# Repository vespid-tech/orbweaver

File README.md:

# orbweaver

Orbweaver is a Sub-GHz HAT+ designed for the Raspberry Pi 5. When loaded with the Orbweaver firmware, it allows users to set-up peer-to-peer mesh networks between Raspberry Pi's, Desktop/Laptops, and Android mobile devices.

# Licensing & Trademarks

### Open Source Components
* **Hardware (`/hardware`)**: All hardware licensed under **CERN Open Hardware Licence Version 2 – Strongly Reciprocal** (`CERN-OHL-S-2.0`).
* **Firmware (`/firmware`)**: All firmware Licensed under the **GNU General Public License v3.0** (`GPL-3.0-only`).
* **Software (`/software`)**: All software Licensed under the **GNU General Public License v3.0** (`GPL-3.0-only`).
* **Documentation (`/documents`)**: All documentation (except the trademarks mentioned below) Licensed under the **Creative Commons Attribution-ShareAlike 4.0 International** (`CC BY-SA 4.0`).
* The full text of these licenses can be found in this repository in the hardware, software, and firmware folders they apply to.

### Non-open Source Components
* **Trademarks:** "Vespid," "Orbweaver," and associated logos are trademarks of Vespid.

# Questions, Info, Help

You can find out more about Vespid online at **[www.vespidtech.com](https://www.vespidtech.com)**.

# Disclaimer

Orbweaver is provided “as is,” without warranty of any kind express or implied. In no event shall Vespid or any Orbweaver developers or contributors be liable for any claim, damages, or other liability arising from its use. Orbweaver is intended for evaluation and development use only. It is not supplied as a finished product and is not certified for use in any product made for sale to the general public. The purchaser is responsible for ensuring that the final configuration (including but not limited to firmware configuration, transmission power, antenna selection, transmission frequency, etc.), complies with applicable regulatory requirements.

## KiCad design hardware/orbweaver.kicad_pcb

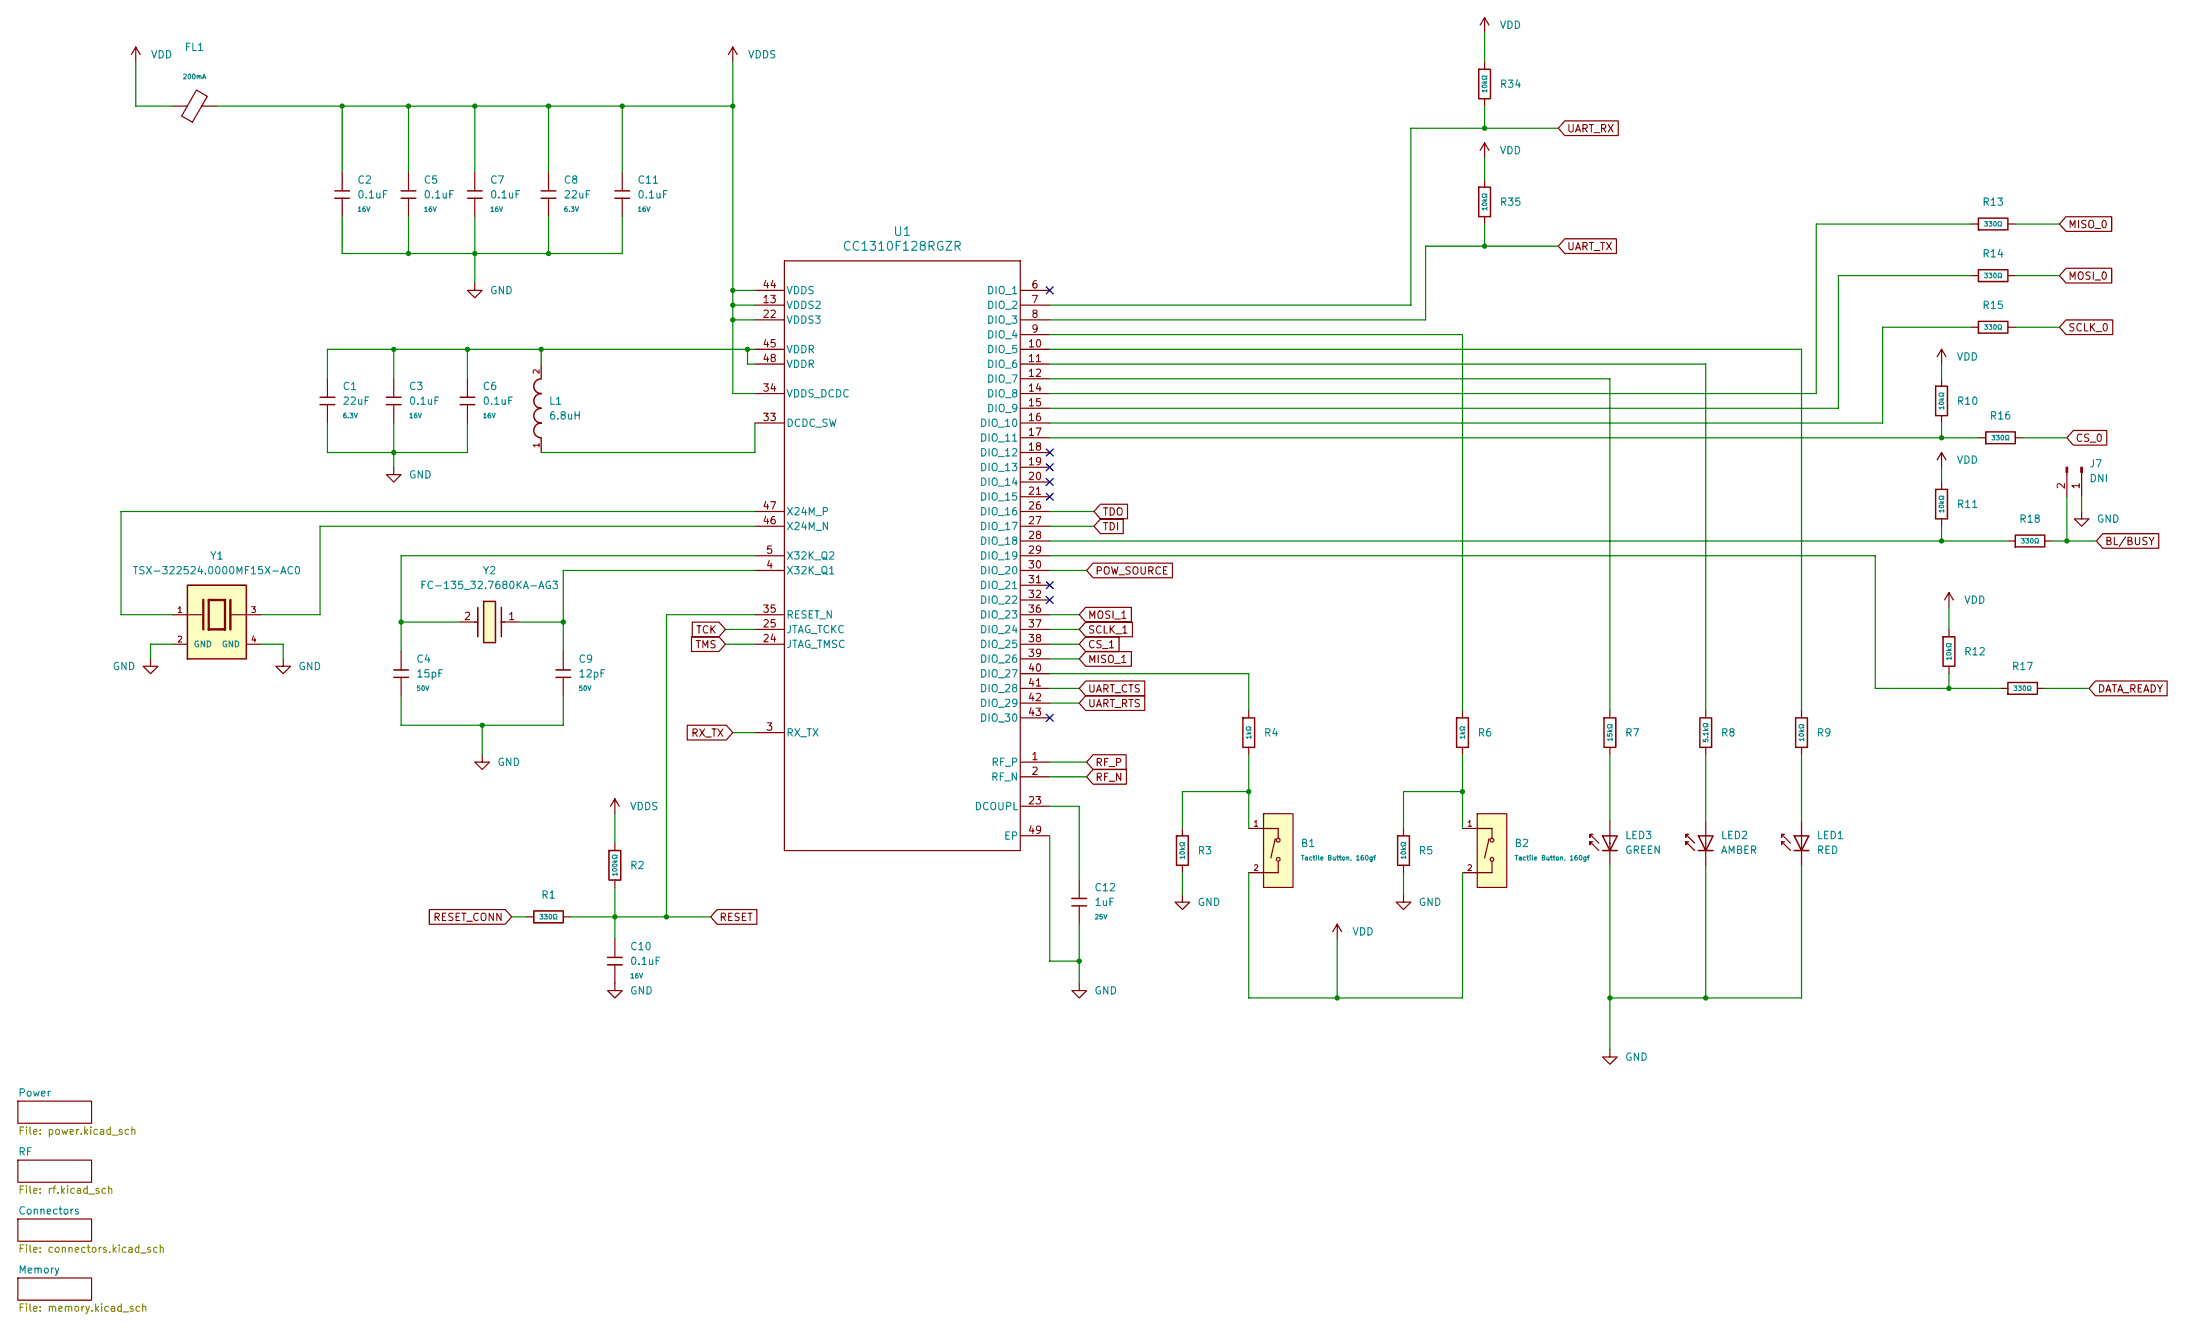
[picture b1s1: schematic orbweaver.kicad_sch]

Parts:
B1, B2: Tactile Button, 160gf; SW_TS-1088-AR02016; Voltage Rating (Dc) 12V; Part TS-1088-AR02016; LCSC C720477
C1, C8: 22uF; C_0603; Voltage Rated 6.3V; Tolerance ±20%; Part CL10A226MQ8NRNC; LCSC C59461
C2, C3, C5, C6, C7, C10, C11: 0.1uF; C_0402; Voltage Rated 16V; Tolerance ±10%; Part CL05B104KO5NNNC; LCSC C1525
C4: 15pF; C_0402; Voltage Rated 50V; Tolerance ±5%; Part 0402CG150J500NT; LCSC C1548
C9: 12pF; C_0402; Voltage Rated 50V; Tolerance ±5%; Part 0402CG120J500NT; LCSC C1547
C12: 1uF; C_0402; Voltage Rated 25V; Tolerance ±10%; Part CL05A105KA5NQNC; LCSC C52923
FL1: FB_0603; Current Rating 200mA; Tolerance ±25%; Part GZ1608D601TF; LCSC C1002
J7: DNI; PinHeader_1x02_P2.54mm_Vertical
L1: 6.8uH; INDC2012X105N; Mouser Part Number 810-MLZ2012N6R8LT000
LED1: RED; D_0805; Forward Voltage (VF) 1.6V~2.6V; Mouser Part Number 941-JE2835ARDN01AN
LED2: AMBER; D_0805; Mouser Part Number 941-JE2835ARDN01AN
LED3: GREEN; D_0805; Mouser Part Number 941-JE2835AGRN02AN
R1, R13, R14, R15, R16: 330Ω; R_0805; Overload Voltage (Max) 150V; Tolerance ±1%; Part 0805W8F1000T5E; LCSC C17408
R2: 100kΩ; R_0402; Overload Voltage (Max) 50V; Tolerance ±1%; Part 0402WGF1003TCE; DigiKey_Part_Number 541-CRCW0402100KFHEDPCT-ND
R3, R5, R9, R10, R11, R12, R34, R35: 10kΩ; R_0805; Overload Voltage (Max) 150V; Tolerance ±1%; Part 0805W8F1002T5E; LCSC C17414
R4, R6: 1kΩ; R_0805; Overload Voltage (Max) 150V; Tolerance ±1%; Part 0805W8F1001T5E; LCSC C17513
R7: 15kΩ; R_0805; Overload Voltage (Max) 150V; Tolerance ±1%; Part 0805W8F1502T5E; LCSC C17475
R8: 5.1kΩ; R_0805; Overload Voltage (Max) 150V; Tolerance ±1%; Part 0805W8F5101T5E; LCSC C27834
R17, R18: 330Ω; R_0805; Overload Voltage (Max) 150V; Tolerance ±1%; Part 0805W8F3300T5E; LCSC C17630
U1: CC1310F128RGZR; Texas_RGZ0048A_VQFN-48-1EP_7x7mm_P0.5mm_EP5.15x5.15mm
Y1: TSX-322524.0000MF15X-AC0; XTAL_TSX-3225_24.0000MF15X-AC0; PARTREV N/A
Y2: FC-135_32.7680KA-AG3; FC135327680KAAG3; Mouser Part Number 732-FC135-32.76KAAG3

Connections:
BL/BUSY: J7.2, R18.2; also elsewhere on the board
CS_0: R16.2; also elsewhere on the board
CS_1: U1.38 (DIO_25); also elsewhere on the board
DATA_READY: R17.2; also elsewhere on the board
GND: C1.1, C2.1, C3.1, C4.1, C5.1, C6.1, C7.1, C8.1, C9.1, C10.1, C11.1, C12.1, J7.1, LED1.1, LED2.1, LED3.1, R3.2, R5.2, U1.49 (EP), Y1.2 (GND), Y1.4 (GND); also elsewhere on the board
MISO_0: R13.2; also elsewhere on the board
MISO_1: U1.39 (DIO_26); also elsewhere on the board
MOSI_0: R14.2; also elsewhere on the board
MOSI_1: U1.36 (DIO_23); also elsewhere on the board
unnamed: B1.1 (A), R3.1, R4.2
unnamed: B2.1 (A), R5.1, R6.2
unnamed: C1.2, C3.2, C6.2, L1.2, U1.45 (VDDR), U1.48 (VDDR)
unnamed: LED1.2, R9.1
unnamed: LED2.2, R8.1
unnamed: LED3.2, R7.2
unnamed: L1.1, U1.33 (DCDC_SW)
unnamed: C12.2, U1.23 (DCOUPL)
unnamed: R6.1, U1.9 (DIO_4)
unnamed: R9.2, U1.10 (DIO_5)
unnamed: R8.2, U1.11 (DIO_6)
unnamed: R7.1, U1.12 (DIO_7)
unnamed: R13.1, U1.14 (DIO_8)
unnamed: R14.1, U1.15 (DIO_9)
unnamed: R15.1, U1.16 (DIO_10)
unnamed: R10.2, R16.1, U1.17 (DIO_11)
unnamed: R11.2, R18.1, U1.28 (DIO_18)
unnamed: R12.2, R17.1, U1.29 (DIO_19)
unnamed: R4.1, U1.40 (DIO_27)
unnamed: U1.46 (X24M_N), Y1.3
unnamed: U1.47 (X24M_P), Y1.1
unnamed: C9.2, U1.4 (X32K_Q1), Y2.1
unnamed: C4.2, U1.5 (X32K_Q2), Y2.2 (CRYSTAL_2)
POW_SOURCE: U1.30 (DIO_20); also elsewhere on the board
RESET: C10.2, R1.2, R2.2, U1.35 (RESET_N); also elsewhere on the board
RESET_CONN: R1.1; also elsewhere on the board
RF_N: U1.2 (RF_N); also elsewhere on the board
RF_P: U1.1 (RF_P); also elsewhere on the board
RX_TX: U1.3 (RX_TX); also elsewhere on the board
SCLK_0: R15.2; also elsewhere on the board
SCLK_1: U1.37 (DIO_24); also elsewhere on the board
TCK: U1.25 (JTAG_TCKC); also elsewhere on the board
TDI: U1.27 (DIO_17); also elsewhere on the board
TDO: U1.26 (DIO_16); also elsewhere on the board
TMS: U1.24 (JTAG_TMSC); also elsewhere on the board
UART_CTS: U1.41 (DIO_28); also elsewhere on the board
UART_RTS: U1.42 (DIO_29); also elsewhere on the board
UART_RX: R34.2, U1.7 (DIO_2); also elsewhere on the board
UART_TX: R35.2, U1.8 (DIO_3); also elsewhere on the board
VDD: B1.2 (B), B2.2 (B), FL1.1, R10.1, R11.1, R12.1, R34.1, R35.1; also elsewhere on the board
VDDS: C2.2, C5.2, C7.2, C8.2, C11.2, FL1.2, R2.1, U1.13 (VDDS2), U1.22 (VDDS3), U1.34 (VDDS_DCDC), U1.44 (VDDS)

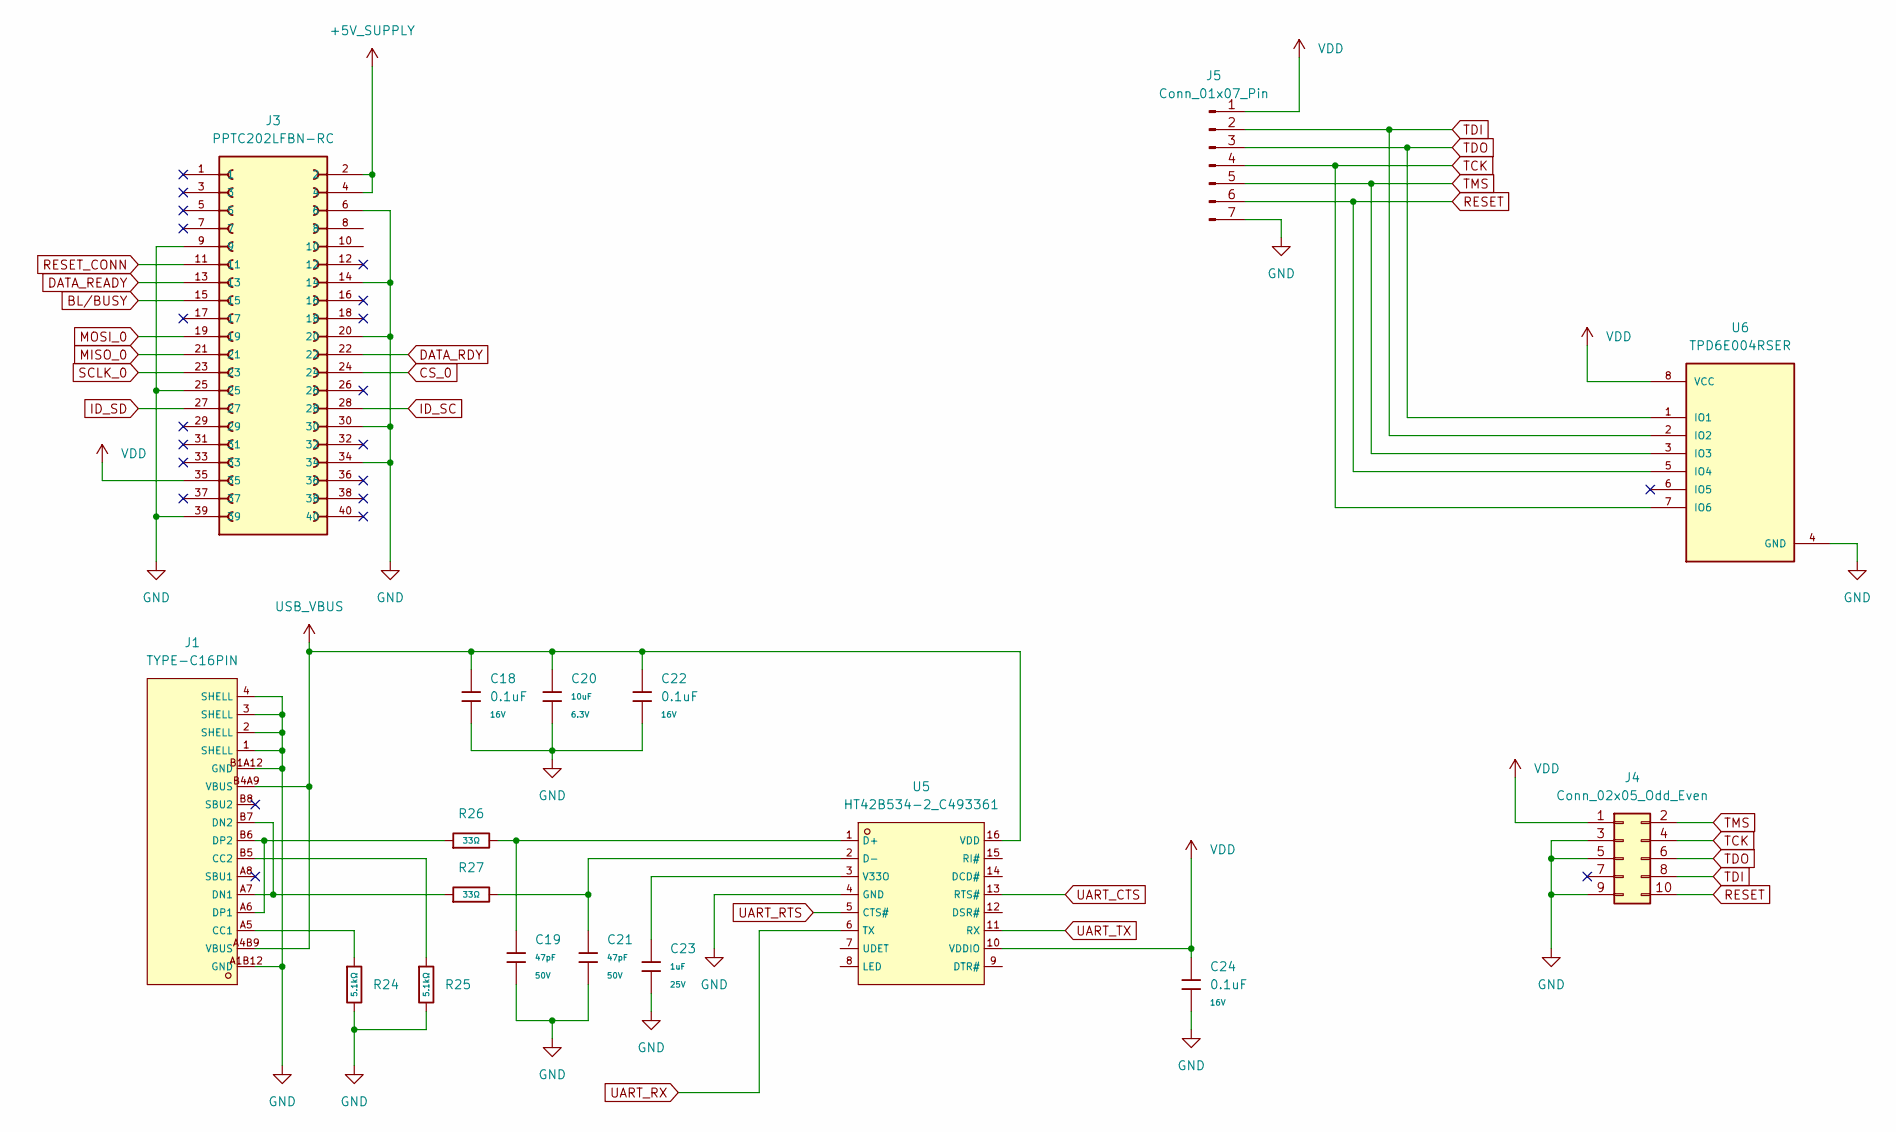
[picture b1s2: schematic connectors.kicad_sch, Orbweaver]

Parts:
C18, C22, C24: 0.1uF; C_0402; Voltage Rated 16V; Tolerance ±10%; Part CL05B104KO5NNNC; LCSC C1525
C19, C21: 47pF; C_0402; Voltage Rated 50V; Tolerance ±5%; Part 0402CG470J500NT; LCSC C1567
C20: 10uF; C_0402; Voltage Rated 6.3V; Tolerance ±20%; Part CL05A106MQ5NUNC; LCSC C15525
C23: 1uF; C_0402; Voltage Rated 25V; Tolerance ±10%; Part CL05A105KA5NQNC; LCSC C52923
J1: TYPE-C16PIN; USB-C-SMD_TYPE-C16PIN; LCSC C393939
J3: PPTC202LFBN-RC; SULLINS_PPTC202LFBN-RC; PARTREV L
J4: Conn_02x05_Odd_Even; PinHeader_2x05_P1.27mm_Vertical_SMD
J5: Conn_01x07_Pin; PinHeader_1x07_P2.54mm_Vertical
R24, R25: 5.1kΩ; R_0402; Overload Voltage (Max) 50V; Tolerance ±1%; Part 0402WGF5101TCE; LCSC C25905
R26, R27: 33Ω; R_0402; Overload Voltage (Max) 50V; Tolerance ±1%; Part 0402WGF330JTCE; LCSC C25105
U5: HT42B534-2_C493361; NSOP-16_L9.9-W3.9-P1.27-LS6.0-BL; LCSC C493361
U6: TPD6E004RSER; IC_TPD6E004RSER; PARTREV 4220323/B 03/2018

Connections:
+5V_SUPPLY: J3.2, J3.4; also elsewhere on the board
BL/BUSY: J3.15; also elsewhere on the board
CS_0: J3.24; also elsewhere on the board
DATA_RDY: J3.22
DATA_READY: J3.13; also elsewhere on the board
GND: C18.1, C19.2, C20.2, C21.2, C22.1, C23.2, C24.1, J1.1 (SHELL), J1.2 (SHELL), J1.3 (SHELL), J1.4 (SHELL), J1.A1B12 (GND), J1.B1A12 (GND), J3.6, J3.9, J3.14, J3.20, J3.25, J3.30, J3.34, J3.39, J4.3, J4.5, J4.9, J5.7, R24.2, R25.2, U5.4 (GND), U6.4 (GND); also elsewhere on the board
ID_SC: J3.28; also elsewhere on the board
ID_SD: J3.27; also elsewhere on the board
MISO_0: J3.21; also elsewhere on the board
MOSI_0: J3.19; also elsewhere on the board
unnamed: J1.A5 (CC1), R24.1
unnamed: J1.B5 (CC2), R25.1
unnamed: J1.A7 (DN1), J1.B7 (DN2), R27.1
unnamed: J1.A6 (DP1), J1.B6 (DP2), R26.1
unnamed: C19.1, R26.2, U5.1 (D+)
unnamed: C21.1, R27.2, U5.2 (D-)
unnamed: C23.1, U5.3 (V33O)
RESET: J4.10, J5.6, U6.5 (IO4); also elsewhere on the board
RESET_CONN: J3.11; also elsewhere on the board
SCLK_0: J3.23; also elsewhere on the board
TCK: J4.4, J5.4, U6.7 (IO6); also elsewhere on the board
TDI: J4.8, J5.2, U6.2 (IO2); also elsewhere on the board
TDO: J4.6, J5.3, U6.1 (IO1); also elsewhere on the board
TMS: J4.2, J5.5, U6.3 (IO3); also elsewhere on the board
UART_CTS: U5.13 (RTS#); also elsewhere on the board
UART_RTS: U5.5 (CTS#); also elsewhere on the board
UART_RX: U5.6 (TX); also elsewhere on the board
UART_TX: U5.11 (RX); also elsewhere on the board
USB_VBUS: C18.2, C20.1, C22.2, J1.A4B9 (VBUS), J1.B4A9 (VBUS), U5.16 (VDD); also elsewhere on the board
VDD: C24.2, J3.35, J4.1, J5.1, U5.10 (VDDIO), U6.8 (VCC); also elsewhere on the board

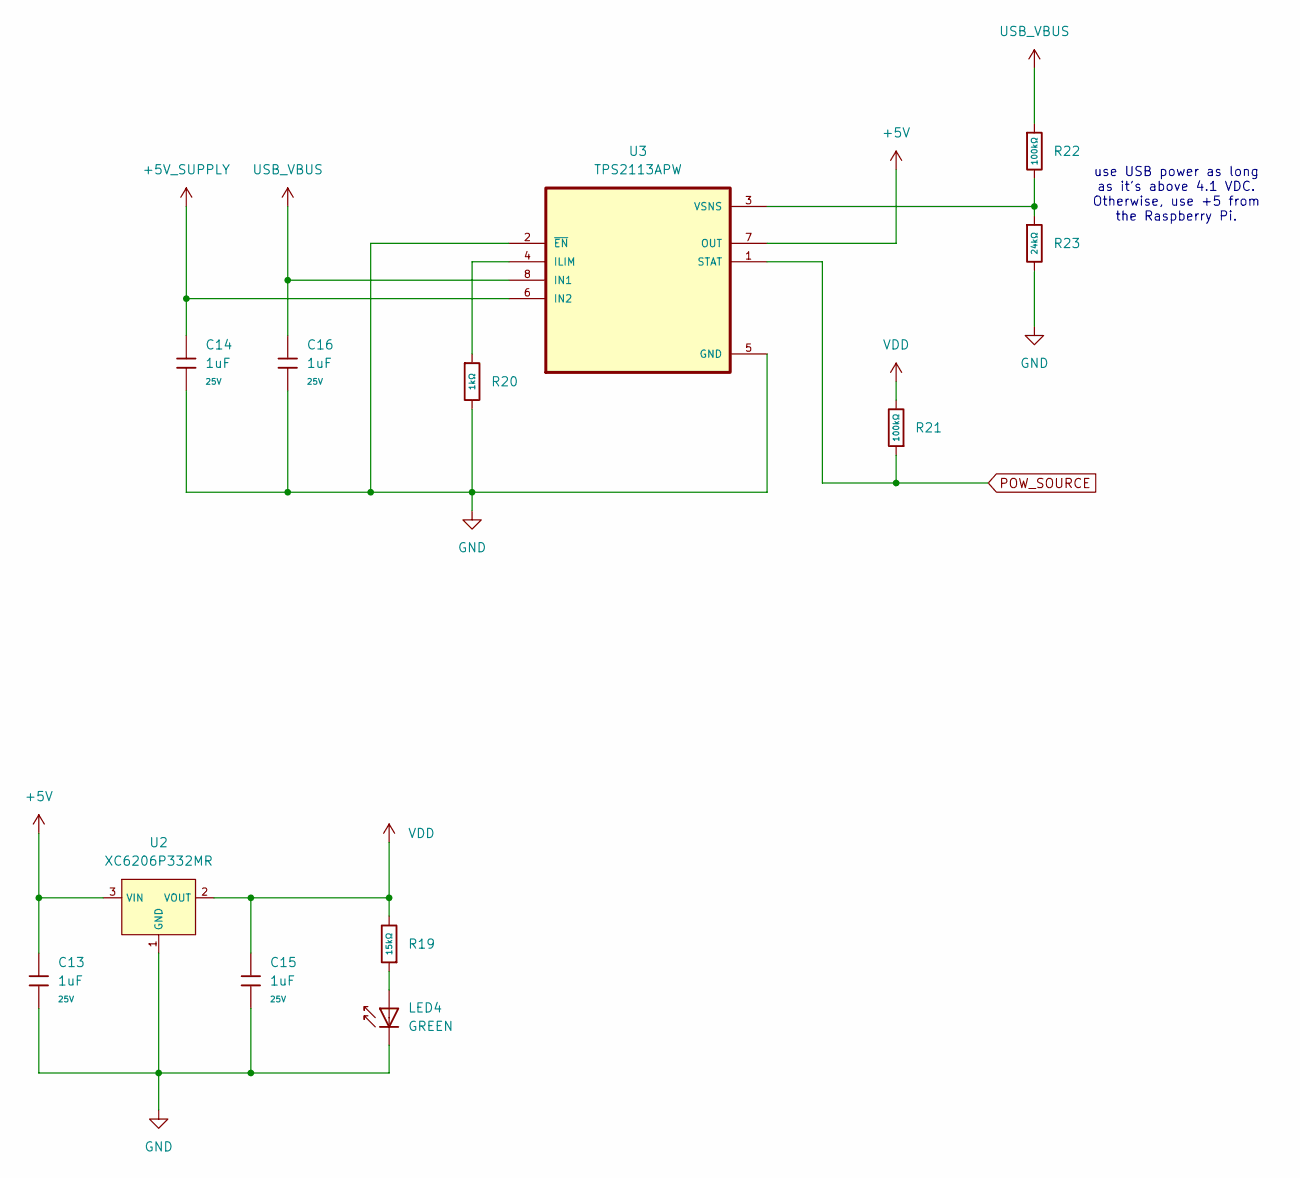
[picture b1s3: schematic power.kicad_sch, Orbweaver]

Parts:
C13, C14, C15, C16: 1uF; C_0805; Voltage Rated 25V; Tolerance ±10%; Part CL05A105KA5NQNC; LCSC C52923
LED4: GREEN; D_0805; Forward Voltage (VF) 1.6V~2.6V; Mouser Part Number 941-JE2835ARDN01AN
R19: 15kΩ; R_0805; Overload Voltage (Max) 150V; Tolerance ±1%; Part 0805W8F1502T5E; LCSC C17475
R20: 1kΩ; R_0805; Overload Voltage (Max) 150V; Tolerance ±1%; Part 0805W8F1001T5E; LCSC C17513
R21, R22: 100kΩ; R_0805; Overload Voltage (Max) 150V; Tolerance ±1%; Part 0805W8F1003T5E; DigiKey_Part_Number 541-CRCW0402100KFHEDPCT-ND
R23: 24kΩ; R_0805; Overload Voltage (Max) 150V; Tolerance ±1%; Part 0805W8F2402T5E; LCSC C17575
U2: XC6206P332MR; SOT-23-3_L2.9-W1.6-P1.90-LS2.8-BR; Output Voltage 3.3V; Dropout Voltage 680mV@(100mA); Part XC6206P332MR-G; LCSC C5446
U3: TPS2113APW; SOP65P640X120-8N

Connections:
+5V: C13.2, U2.3 (VIN), U3.7 (OUT)
+5V_SUPPLY: C14.2, U3.6 (IN2); also elsewhere on the board
GND: C13.1, C14.1, C15.1, C16.1, LED4.1, R20.2, R23.2, U2.1 (GND), U3.2 (~EN), U3.5 (GND); also elsewhere on the board
unnamed: LED4.2, R19.1
unnamed: R20.1, U3.4 (ILIM)
unnamed: R22.2, R23.1, U3.3 (VSNS)
POW_SOURCE: R21.1, U3.1 (STAT); also elsewhere on the board
USB_VBUS: C16.2, R22.1, U3.8 (IN1); also elsewhere on the board
VDD: C15.2, R19.2, R21.2, U2.2 (VOUT); also elsewhere on the board

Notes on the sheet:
use USB power as long as it's above 4.1 VDC. Otherwise, use +5 from the Raspberry Pi.

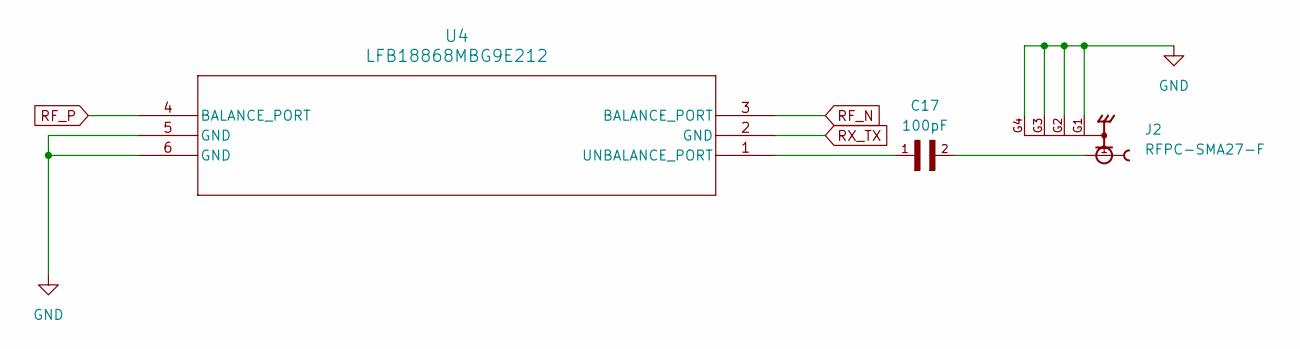
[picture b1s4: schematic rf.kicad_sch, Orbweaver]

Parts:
C17: 100pF; C_0805
J2: RFPC-SMA27-F; GRADCONN_RFPC-SMA27-F; PARTREV 1.0
U4: LFB18868MBG9E212; LFB18868MBG9E212_MUR

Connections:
GND: J2.G1, J2.G2, J2.G3, J2.G4, U4.5 (GND), U4.6 (GND); also elsewhere on the board
unnamed: C17.2, J2.1
unnamed: C17.1, U4.1 (UNBALANCE_PORT)
RF_N: U4.3 (BALANCE_PORT); also elsewhere on the board
RF_P: U4.4 (BALANCE_PORT); also elsewhere on the board
RX_TX: U4.2 (GND); also elsewhere on the board

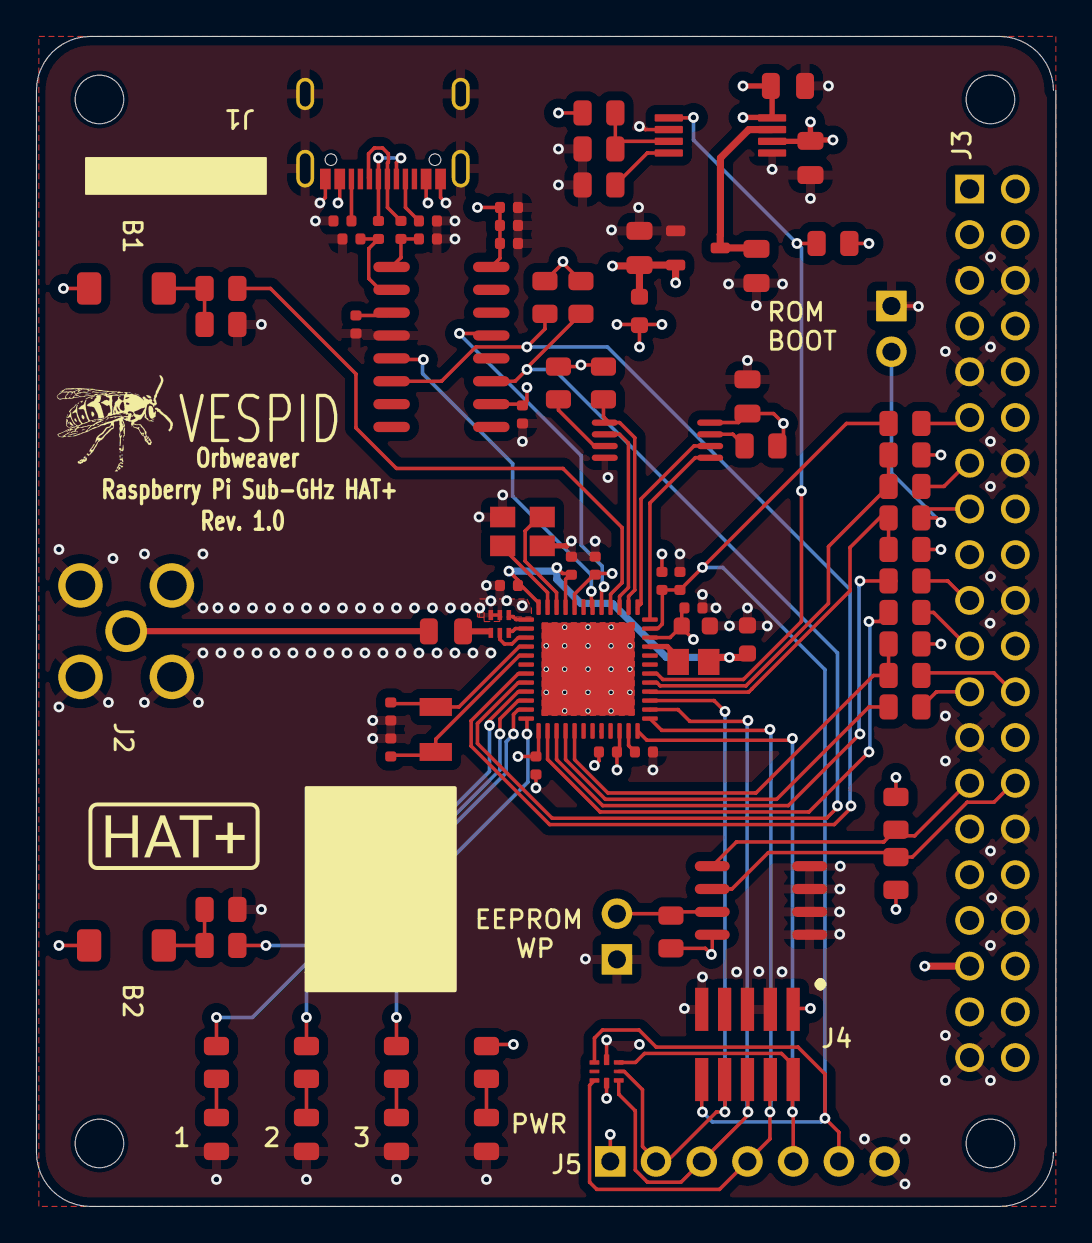
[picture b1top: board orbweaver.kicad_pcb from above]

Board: 4 copper layers, 56.6 x 65.0 mm, 85 parts (1 on the bottom side), 70 nets.

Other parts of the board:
C25: 0.1uF; C_0805
IC1: ZD25WQ80COIGR; TSSOP-8_L4.4-W3.0-P0.65-LS6.4-BL
J6: DNI; PinHeader_1x02_P2.54mm_Vertical
R28, R29, R32: 5.1kΩ; R_0805
R30: 1kΩ; R_0805
R31, R33: 3.9kΩ; R_0805
U7: CAT24C32WI-GT3; SOIC-8_L5.0-W4.0-P1.27-LS6.0-BL

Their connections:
CS_1: IC1.1 (CS#), R29.2; also elsewhere on the board
GND: C25.1, IC1.4 (VSS), J6.1, U7.1 (A0), U7.2 (A1), U7.3 (A2), U7.4 (VSS); also elsewhere on the board
ID_SC: R31.2, U7.6 (SCL); also elsewhere on the board
ID_SD: R33.2, U7.5 (SDA); also elsewhere on the board
MISO_1: IC1.2 (SO/IO1); also elsewhere on the board
MOSI_1: IC1.5 (SI/IO0); also elsewhere on the board
unnamed: IC1.7 (HOLD#/IO3), R32.2
unnamed: IC1.3 (WP#/IO2), R28.2
unnamed: J6.2, R30.2, U7.7 (WP)
SCLK_1: IC1.6 (SCLK); also elsewhere on the board
VDD: C25.2, IC1.8 (VCC), R28.1, R29.1, R30.1, R31.1, R32.1, R33.1, U7.8 (VCC); also elsewhere on the board

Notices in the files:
hardware/connectors.kicad_sch:
License: CERN-OHL-S-2.0
